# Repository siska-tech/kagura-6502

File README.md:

# KAGURA-6502

KAGURA-6502 は、実物の W65C02S を CPU に使う自作 6502 コンピュータです。専用キャリア基板 Rev.A に Tang Nano 9K と XIAO RP2040 を組み合わせ、HDMI ディスプレイと USB キーボードで使えるスタンドアロンの BASIC 機を目指しています。

*キャリア基板 Rev.A（72 × 48 mm、4 層）の設計データから生成したイメージ。*

| 構成 | 役割 |
| --- | --- |
| W65C02S | 3.375 MHz で BIOS と KAGURA BASIC を実行 |
| Tang Nano 9K | CPU バス、PSRAM 主記憶、8 KiB 高速 RAM、2 KiB Boot ROM。320×176 のタイル・スプライト映像を HDMI 720p60 で出力し、6ch 音源を HDMI / PWM に出力 |
| XIAO RP2040 | CPU のリセットを監督。キャリア基板の USB-A にキーボードをつなぐための配線を備える |

**RTL v1.0 RC は W65C02S 実機照合待ちです。** 現行版のコンソールは Tang Nano 9K の USB シリアルです。BIOS から KAGURA BASIC を UART でロードします。基板上の USB-A からキー入力を使うには、XIAO の USB ホスト／HID ファームウェアと、FPGA のコンソール入力経路の実装が必要です。

[GitHub Releases](https://github.com/siska-tech/kagura-6502/releases/tag/v1.0-rc.1) で bitstream、ガーバー・ドリル、組み立て指南書をまとめて配布しています。回路図と PCB は [KiCad プロジェクト](board/kagura-6502.kicad_pro) を開いて確認できます。

## KAGURA-6502 の仕様諸元

以下は公開 bitstream `aud_p1024.fs` とキャリア基板 Rev.A の組み合わせです。

| 項目 | 仕様 |
| --- | --- |
| CPU | WDC W65C02S（DIP-40、3.3 V）。PHI2 は公称 3.375 MHz（54 MHz ÷ 16）。PSRAM アクセスの待ち時間に応じて PHI2 を伸長 |
| 主記憶 | Tang Nano 9K 内蔵 PSRAM のうち 4 MiB を使用。CPU の 64 KiB アドレス空間から 4 KiB のバンク窓で全域にアクセス |
| 高速 RAM / ROM | FPGA 内蔵 BSRAM に高速 RAM 8 KiB と BIOS ROM 2 KiB。高速 RAM、ROM、I/O は PHI2 の伸長なし |
| 起動と BASIC | Boot ROM の BIOS が起動し、UART ローダから PSRAM へ BASIC イメージを転送。KAGURA BASIC は Microsoft BASIC 1.1 系の msbasic をベースとし、インタプリタのコードを高速 RAM に置く構成も選択可能 |
| 映像出力 | HDMI 1280×720、60 Hz、ピクセルクロック 74.25 MHz。論理画面は 320×180 の 4 倍拡大で、上下各 2 論理ラインを除く 320×176 が描画領域 |
| 背景 | 8×8 ピクセルのタイル、表示範囲 40×22 タイル。1024 パターン（32 KiB）、4 bpp、16 色×16 パレット（RGB565）。水平・垂直スクロール、ボーダー色、VBLANK 割り込み |
| スプライト | 256 個を登録でき、1 ラインに最大 64 個を表示。8×8 または 16×16 ピクセル、水平・垂直反転 |
| 音源 | 6 ch（矩形波 3、15 ビット LFSR ノイズ 1、波形 2）。波形は各 256 サンプル。48 kHz・符号付き 16 ビットのステレオ PCM を HDMI へ送り、同じ音声を左右の PWM へ出力 |
| コンソール | Tang Nano 9K の USB-C 経由で BL702 USB-UART を使用。115200 baud、8N1 |
| 基板と外部端子 | キャリア基板 Rev.A、約 72×48 mm、4 層。Tang 側の HDMI と USB-C、キャリア側の USB-A、3.3 V SPI 拡張、PWM／デバッグヘッダ、外付けボタン端子 |
| リセットと給電 | XIAO RP2040 が FPGA の UART 状態フレームを監視して CPU の RESB を解除。主電源は Tang の USB-C。XIAO の給電経路は JP1 で選択し、USB-A の VBUS は Tang 側 5 V から PTC 経由で供給 |

### CPU メモリマップ

| CPU アドレス | 割り当て |
| --- | --- |
| `$0000–$1FFF` | 高速 RAM（ゼロページとスタックを含む） |
| `$2000–$BFFF`、`$E000–$F7FF` | PSRAM の直接アクセス領域。BASIC イメージの基準位置は `$9800` |
| `$C000–$CFFF` | PSRAM の 4 KiB バンク窓。バンク番号は `$D005–$D006` |
| `$D000–$D00F` | システム I/O。コンソール UART は `$D00A–$D00B`、PSRAM 書き込み保護は `$D00C` |
| `$D300–$D33F` | VDP。VRAM のアドレス／データ、表示・スクロール・割り込み、波形 2 ch の制御を含む |
| `$D400–$D41F` | 矩形波・ノイズ・マスター音量の制御。`$D41F` への書き込みで設定を一括反映 |
| `$F800–$FFFF` | BIOS ROM と CPU ベクタ |

詳細資料

- [VDP と VRAM](docs/vdp.md) — 画面座標、レジスタ、タイル・スプライトのデータ形式
- [6ch 音源](docs/audio.md) — レジスタ、波形メモリ、ミックスと設定反映
- [BIOS・BASIC と実機起動](docs/boot-and-basic.md) — 起動時の確認、BASIC イメージの生成と UART ローダの仕様
- [ピン割当](docs/pinmap.md) と [基板の組み立て指南書](board/README.md) — コネクタ、給電、初回通電

## 検証状況

この RC の bitstream は [aud_p1024.fs](release/aud_p1024.fs) の 1 点です。[SHA-256](release/SHA256SUMS) を照合できます。RTL の基準はローカル実装コミット `fdbc3a0`、Gowin Commercial 1.9.12.04、place option 2 / route option 1 です。保存済みの [統合シミュレーション](build-logs/audio/sim_system/sys_a1024_aud.log) は PASS、[STA](build-logs/audio/aud_p1024/aud_p1024.tr) は Setup / Hold 違反 0 / 0、[資源レポート](build-logs/audio/aud_p1024/aud_p1024.rpt.txt) は BSRAM 26 / 26 です。実機での CPU 起動、PSRAM、映像・音声は未確認です。波形チャンネルは 256 サンプル固定です。

**Tang Nano 9K の TF スロットにカードを挿さないでください。** CPU アドレス線 A8–A11 と信号を共有します。[ピン割当](docs/pinmap.md) を参照してください。

## 再現

Gowin Commercial 1.9.12.04 と Git Bash で `bash fpga/audio/syn/build_audio.sh aud_p1024` を実行します。生成先は `fpga/audio/syn/impl_aud_p1024/impl/pnr/aud_p1024.fs` です。保存レポートはビルド時に更新されます。

統合シミュレーションは WSL 上の Verilator 5.032 を使用します。ローカルの 6502-sim リポジトリを環境変数 `SIM6502` で指定してください。スクリプトがコミット `f00df4cb3bf639270f294965de1dea98bb55cfce` を参照します。

```sh
bash fpga/tools/build_cc65.sh
bash fpga/basic/sw/build_sw.sh
bash fpga/audio/sim/run_audio.sh all
bash fpga/vdp/sim/run_system.sh sys_a1024_aud
```

第三者ソースの表示とライセンスは [THIRD_PARTY.md](THIRD_PARTY.md) を参照してください。KAGURA-6502 自体のライセンスは未決定です。

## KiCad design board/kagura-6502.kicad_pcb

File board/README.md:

# KAGURA-6502 キャリア基板 Rev.A（設計版 0.5）

KiCad 10 用の基板ソースは [board ディレクトリ](https://github.com/siska-tech/kagura-6502/tree/main/board) にあります。
基板は 72 × 48 mm、4 層。表裏に GND ゾーンを配置した。上下の長辺から内側へ各 2 mm をケースの支持帯とし、全銅箔層で配線・ビア・パッド・ベタを禁止した。部品も禁止領域の内側に置かない。
[ピン割当表](https://github.com/siska-tech/kagura-6502/blob/main/docs/pinmap.md) に従い、W65C02S DIP-40、Tang Nano 9K、
XIAO RP2040 を接続する。HDMI 映像・音声には Tang のコネクタを使用する。

| 参照 | 部品・用途 |
| --- | --- |
| U1 | W65C02S DIP-40（15.24 mm 列間隔）。Tang の直下に配置。Tang 側には CPU とソケットの積み上げ高さを超える高さのソケットを使用する |
| J5、J6 | Tang 用 1×24、2.54 mm ソケット。USB-C を左、HDMI を右、部品面を上にする。上段が J6、下段が J5。各 1 番は左 |
| U2 | XIAO RP2040 を表面に直付け。USB-C は右端。W65C02S と長手方向の中心線を共有 |
| J3 | 外付けモーメンタリスイッチ。1: USER_BTN_N、2: GND |
| J4 | デバッグ。1: GND、2–3: PWM L/R、4–7: DBG0–3。すべて入力専用プローブで観測する（信号は 1.8 V） |
| JP1 | XIAO 給電ジャンパ |
| D1 | SS14。帯（カソード）を 1 番パッド側にする |
| R1、R3 | 3.3 kΩ |
| R2、R4–R7 | 10 kΩ |
| R8 | 33 Ω、PHI2 直列 |
| C1、C2 | 100 nF、10 µF。いずれも無極性 MLCC |
| J7 | USB Type-A ホスト、TE 292303-7。XIAO D4/D5 が D+/D− |
| J8 | 3.3 V SPI 汎用拡張ヘッダ（2.54 mm、6 ピン）。1: 3V3、2: GND、3: CS、4: SCK、5: MOSI、6: MISO |
| F1 | USB VBUS の 500 mA 保持 PTC。1206L050/15YR |
| R9、R10 | USB データ線の 22 Ω 直列抵抗 |
| R11、R12 | USB データ線の 15 kΩ プルダウン |

[Pico Carrier Board](https://github.com/siska-tech/kagura/tree/main/boards/pico-carrier-board) を参考に、Tang を上側、USB-A を左側に配置した。XIAO の直付けランドは参照基板と同寸で、KAGURA-6502 では基板表面の右端に配置した。Tang と XIAO の積み上げ高さ、および USB-C プラグの逃げを実装前に確認する。J5/J6 は幅 2.54 mm のソケットを想定している。

Tang は [Sipeed の外形図](https://dl.sipeed.com/fileList/TANG/Nano%209K/4_Dimensional_drawing/Tang_Nano_9K_3672_size.pdf) を参照し、ソケット列間隔を 22.86 mm とした。
XIAO のピン配列は [Seeed のピンアウト](https://wiki.seeedstudio.com/XIAO-RP2040/) を参照した。
発注前に両モジュールを現物と照合し、列間隔、1 番ピン、ソケット高さ、裏面部品とケーブルの逃げを確認する。

Tang の USB-C を主電源とし、J6-24 の 3.3 V を CPU に供給する。JP1 を閉じると
J6-18 の 5 V が D1 経由で XIAO に供給される。JP1 は初期状態では開放し、
使用する Tang のリビジョンで J6-18 の電圧と負荷時の電流余裕を確認してから閉じる。
XIAO を USB 接続する際は JP1 を開放する。給電されていないモジュールに
接続先から信号を入れないよう、XIAO 単体で書き込む場合はTang 側の信号への逆給電を避けられる状態で作業する。
Tang の TF スロットは CPU のアドレス線と共有するため、カードは挿さない。

USB ホストの VBUS は Tang の J6-18 から F1 を経由して供給する。
F1 はリセット可能な過電流保護で、Tang が 500 mA を給電できることを保証するものではない。
周辺機器を接続する前に Tang の 5 V 出力を負荷時に確認する。
USB ホストと SPI 周辺機器の利用には XIAO 側の対応ファームウェアが必要。
J8 は 3.3 V ロジック専用。標準の4ピン Grove とは機械的・電気的に互換性がない。

| 参照 | JLCPCB 部品番号 | 分類 |
| --- | --- | --- |
| R1、R3 | [C22978](https://jlcpcb.com/partdetail/23705-0603WAF3301T5E/C22978) | Basic |
| R2、R4–R7 | [C25804](https://jlcpcb.com/partdetail/C25804) | Basic |
| R8 | [C23140](https://jlcpcb.com/partdetail/0603WAF330JT5E/C23140) | Basic |
| R9、R10 | [C23345](https://jlcpcb.com/partdetail/C23345) | Basic |
| R11、R12 | [C22809](https://jlcpcb.com/partdetail/0603WAF1502T5E/C22809) | Basic |
| C1 | [C14663](https://jlcpcb.com/partdetail/C14663) | Basic |
| C2 | [C15850](https://jlcpcb.com/partdetail/C15850) | Basic |
| D1 | [C2480](https://jlcpcb.com/partdetail/C2480) | Basic |
| F1 | [C151162](https://jlcpcb.com/partdetail/Littelfuse-1206L05015YR/C151162) | Extended |

J7 は機械固定脚付きの SMT コネクタで、モジュール用ソケット類とともに別途手配する。

KiCad 10.0.8 の ERC、DRC、未配線、回路図と PCB の照合はすべて 0 件。
シンボルのピンは接続表に基づく受動型なので、ERC は信号方向や電源容量を検証しない。
初回通電では電源電圧、RESB の起動シーケンス、PHI2 の波形を確認する。
実機での嵌合・通電は未検証。

## 組み立てと初回確認

1. ガーバー ZIP を基板メーカーに渡し、4 層の銅箔、外形、PTH と NPTH のドリルが認識され、外形が 72 × 48 mm であることを確認する。
2. 背の低い部品から実装する。D1 の帯と CPU の 1 番ピンを基板の表示と照合する。Tang のソケットと CPU ソケットを仮置きし、重なりとコネクタの逃げを確認してからはんだ付けする。
3. 通電前に電源と GND の短絡を確認し、JP1 は開放する。モジュールを接続する前にピン番号と向きを確認する。XIAO の独立給電時は逆給電に注意する。
4. Tang Nano 9K 用の aud_p1024.fs の SHA-256 を確認して書き込む。CPU の電源、RESB、PHI2 を確認し、続いて HDMI 映像・音声と CPU の起動を確認する。リポジトリ内の XIAO スクリプトは Phase 1 向けで、現行 RC との組み合わせは未確認。

この配布版は W65C02S 実機照合待ちです。

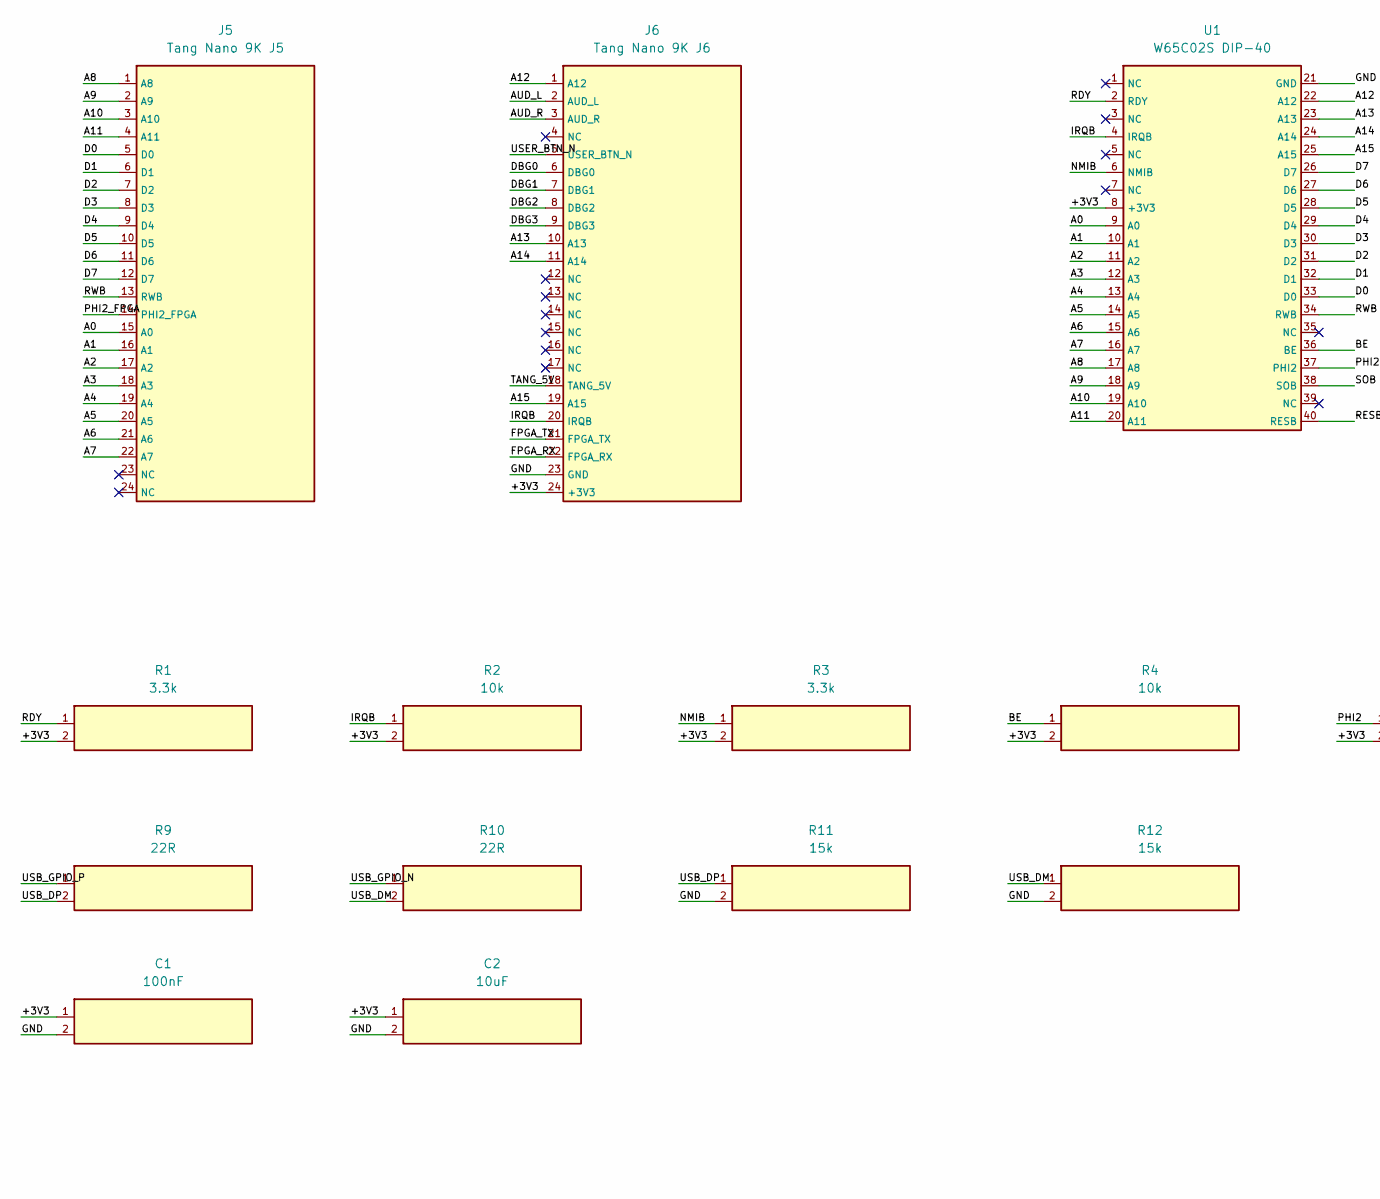
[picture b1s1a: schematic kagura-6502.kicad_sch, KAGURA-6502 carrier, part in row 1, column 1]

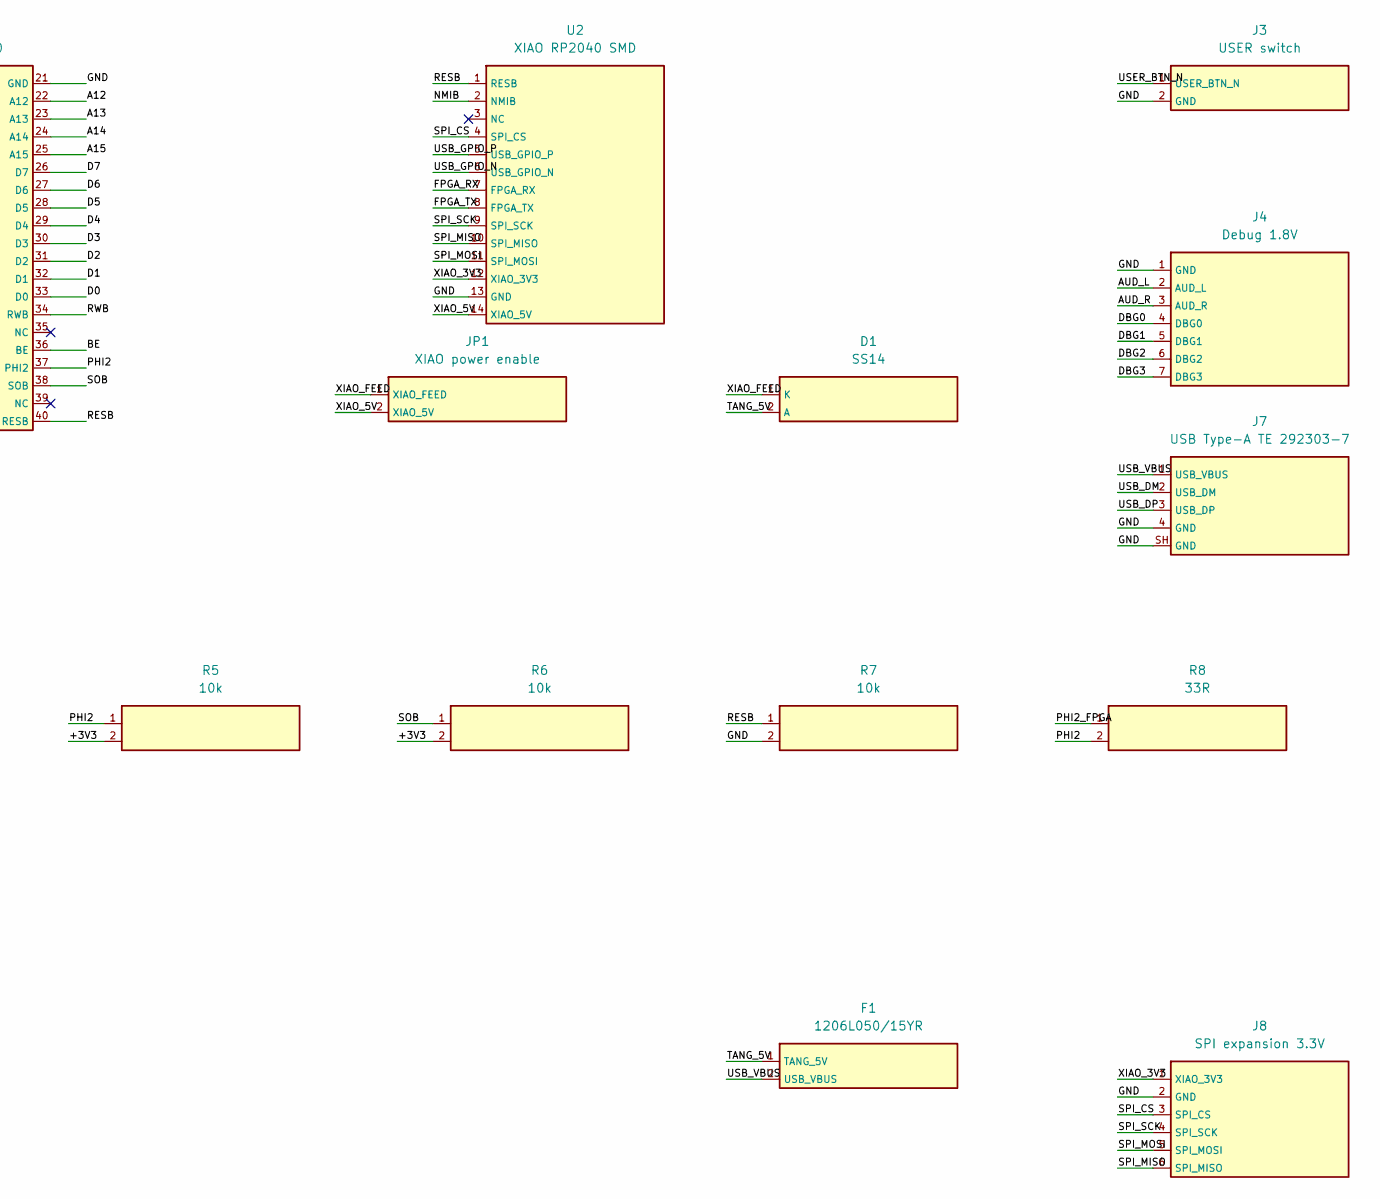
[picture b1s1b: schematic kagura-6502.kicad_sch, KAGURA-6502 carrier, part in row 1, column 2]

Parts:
C1: 100nF; C_0603_1608Metric
C2: 10uF; C_0805_2012Metric
D1: SS14; D_SMA
F1: 1206L050/15YR; Fuse_1206_3216Metric
J3: USER switch; PinHeader_1x02_P2.54mm_Vertical
J4: Debug 1.8V; PinHeader_1x07_P2.54mm_Vertical
J5: Tang Nano 9K J5; PinSocket_1x24_P2.54mm_Vertical
J6: Tang Nano 9K J6; PinSocket_1x24_P2.54mm_Vertical
J7: USB Type-A TE 292303-7; USB_A_TE_292303-7_Horizontal
J8: SPI expansion 3.3V; PinHeader_1x06_P2.54mm_Vertical
JP1: XIAO power enable; PinHeader_1x02_P2.54mm_Vertical
R1, R3: 3.3k; R_0603_1608Metric
R2, R4, R5, R6, R7: 10k; R_0603_1608Metric
R8: 33R; R_0603_1608Metric
R9, R10: 22R; R_0603_1608Metric
R11, R12: 15k; R_0603_1608Metric
U1: W65C02S DIP-40; DIP-40_W15.24mm
U2: XIAO RP2040 SMD; XIAO_RP2040

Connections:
/+3V3: C1.1, C2.1, J6.24 (+3V3), R1.2, R2.2, R3.2, R4.2, R5.2, R6.2, U1.8 (+3V3)
/A0: J5.15 (A0), U1.9 (A0)
/A1: J5.16 (A1), U1.10 (A1)
/A2: J5.17 (A2), U1.11 (A2)
/A3: J5.18 (A3), U1.12 (A3)
/A4: J5.19 (A4), U1.13 (A4)
/A5: J5.20 (A5), U1.14 (A5)
/A6: J5.21 (A6), U1.15 (A6)
/A7: J5.22 (A7), U1.16 (A7)
/A8: J5.1 (A8), U1.17 (A8)
/A9: J5.2 (A9), U1.18 (A9)
/A10: J5.3 (A10), U1.19 (A10)
/A11: J5.4 (A11), U1.20 (A11)
/A12: J6.1 (A12), U1.22 (A12)
/A13: J6.10 (A13), U1.23 (A13)
/A14: J6.11 (A14), U1.24 (A14)
/A15: J6.19 (A15), U1.25 (A15)
/AUD_L: J4.2 (AUD_L), J6.2 (AUD_L)
/AUD_R: J4.3 (AUD_R), J6.3 (AUD_R)
/BE: R4.1, U1.36 (BE)
/D0: J5.5 (D0), U1.33 (D0)
/D1: J5.6 (D1), U1.32 (D1)
/D2: J5.7 (D2), U1.31 (D2)
/D3: J5.8 (D3), U1.30 (D3)
/D4: J5.9 (D4), U1.29 (D4)
/D5: J5.10 (D5), U1.28 (D5)
/D6: J5.11 (D6), U1.27 (D6)
/D7: J5.12 (D7), U1.26 (D7)
/DBG0: J4.4 (DBG0), J6.6 (DBG0)
/DBG1: J4.5 (DBG1), J6.7 (DBG1)
/DBG2: J4.6 (DBG2), J6.8 (DBG2)
/DBG3: J4.7 (DBG3), J6.9 (DBG3)
/FPGA_RX: J6.22 (FPGA_RX), U2.7 (FPGA_RX)
/FPGA_TX: J6.21 (FPGA_TX), U2.8 (FPGA_TX)
/GND: C1.2, C2.2, J3.2 (GND), J4.1 (GND), J6.23 (GND), J7.4 (GND), J7.SH (GND), J8.2 (GND), R7.2, R11.2, R12.2, U1.21 (GND), U2.13 (GND)
/IRQB: J6.20 (IRQB), R2.1, U1.4 (IRQB)
/NMIB: R3.1, U1.6 (NMIB), U2.2 (NMIB)
/PHI2: R5.1, R8.2, U1.37 (PHI2)
/PHI2_FPGA: J5.14 (PHI2_FPGA), R8.1
/RDY: R1.1, U1.2 (RDY)
/RESB: R7.1, U1.40 (RESB), U2.1 (RESB)
/RWB: J5.13 (RWB), U1.34 (RWB)
/SOB: R6.1, U1.38 (SOB)
/SPI_CS: J8.3 (SPI_CS), U2.4 (SPI_CS)
/SPI_MISO: J8.6 (SPI_MISO), U2.10 (SPI_MISO)
/SPI_MOSI: J8.5 (SPI_MOSI), U2.11 (SPI_MOSI)
/SPI_SCK: J8.4 (SPI_SCK), U2.9 (SPI_SCK)
/TANG_5V: D1.2 (A), F1.1 (TANG_5V), J6.18 (TANG_5V)
/USB_DM: J7.2 (USB_DM), R10.2, R12.1
/USB_DP: J7.3 (USB_DP), R9.2, R11.1
/USB_GPIO_N: R10.1, U2.6 (USB_GPIO_N)
/USB_GPIO_P: R9.1, U2.5 (USB_GPIO_P)
/USB_VBUS: F1.2 (USB_VBUS), J7.1 (USB_VBUS)
/USER_BTN_N: J3.1 (USER_BTN_N), J6.5 (USER_BTN_N)
/XIAO_3V3: J8.1 (XIAO_3V3), U2.12 (XIAO_3V3)
/XIAO_5V: JP1.2 (XIAO_5V), U2.14 (XIAO_5V)
/XIAO_FEED: D1.1 (K), JP1.1 (XIAO_FEED)

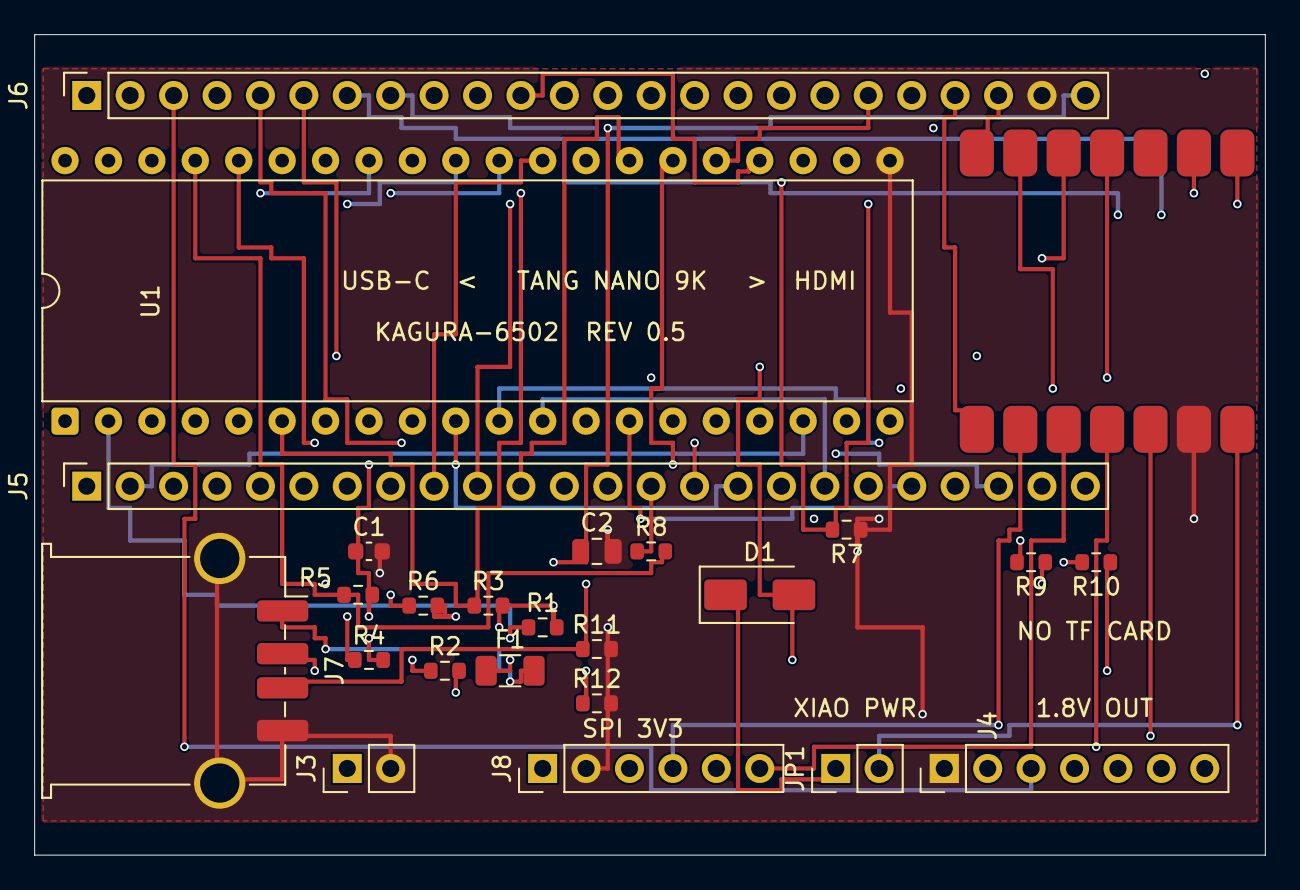
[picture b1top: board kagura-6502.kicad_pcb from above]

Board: 4 copper layers, 72.0 x 48.0 mm, 25 parts (0 on the bottom side), 57 nets.
